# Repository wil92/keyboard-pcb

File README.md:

# keyboard-pcb

A compendium of project about DIY keyboards base on STM32 chips.

> The gerber files are provided and you can use it to replicate the keyboard.

> Also the 3D model for the keyboard is provided in the repository.

## Keyboard Alphanum

This is the first keyboard I made. I decided to get an easy option where I can start my incursion on this work of keyboards.
This keyboard could be used as a USB Hub and is a fun project to be made.

## Keyboard Personal

This is a version of 75% keyboard (with some variations).

## Keyboard Split

tbd

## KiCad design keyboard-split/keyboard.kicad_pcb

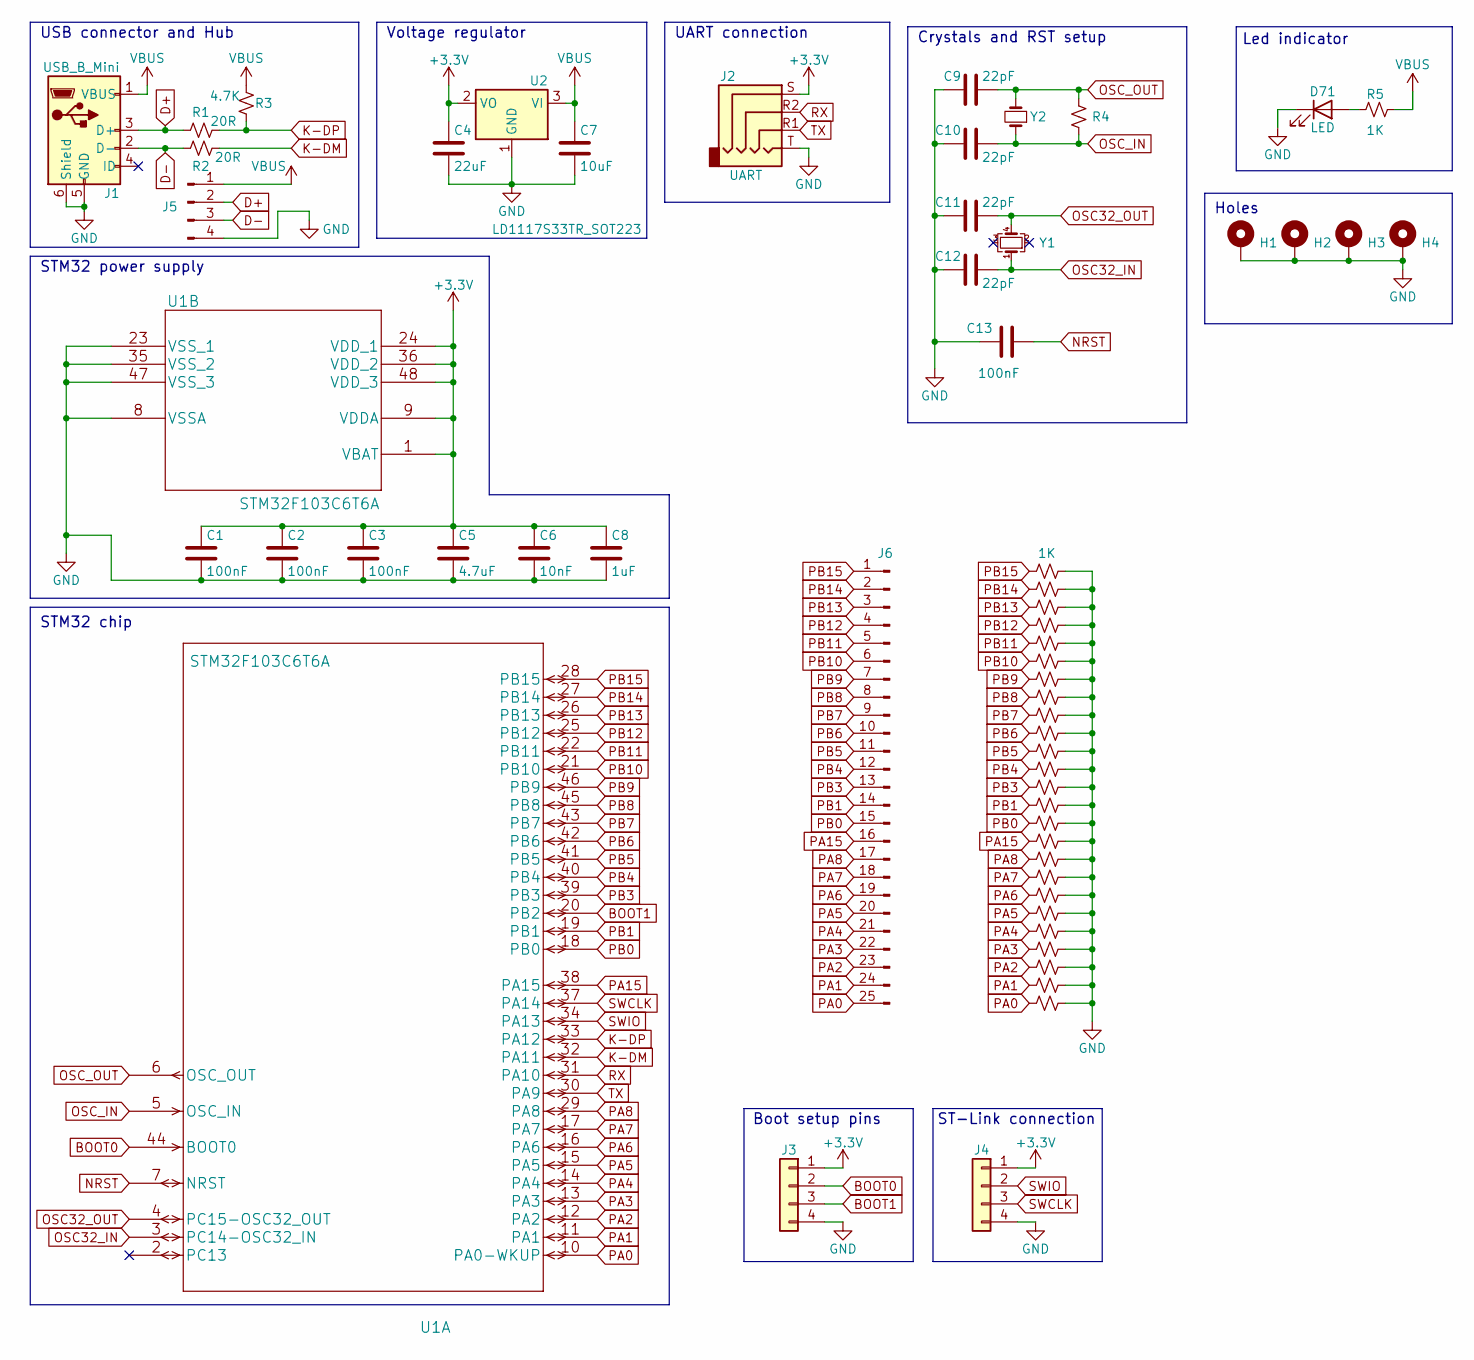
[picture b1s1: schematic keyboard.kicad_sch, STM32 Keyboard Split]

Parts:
C1, C2, C3, C13: 100nF; C_0805_2012Metric
C4: 22uF; C_1206_3216Metric
C5: 4.7uF; C_0805_2012Metric
C6: 10nF; C_0805_2012Metric
C7: 10uF; C_1206_3216Metric
C8: 1uF; C_0805_2012Metric
C9, C10, C11, C12: 22pF; C_0805_2012Metric
D71: LED; LED_0805_2012Metric
H1, H2, H3, H4: MountingHole; MountingHole_3.2mm_M3_DIN965_Pad
J1: USB_B_Mini; USB_Micro-B_A01SB141B1-245
J2: UART; PJ320D
J3, J4: Conn_01x04; PinHeader_1x04_P2.54mm_Vertical
J5: Conn_01x04_Pin; PinSocket_1x04_P1.27mm_Vertical
J6: Conn_01x25_Pin; PinHeader_1x25_P2.54mm_Vertical
R1, R2: 20R; R_0805_2012Metric
R3: 4.7K; R_0805_2012Metric
R4: R_Small_US; R_0805_2012Metric
R5, R6, R7, R8, R9, R10, R11, R12, R13, R14, R15, R16, R17, R18, R19, R20, R21, R22, R23, R24, R25, R26, R27, R28, R29, R30: 1K; R_0805_2012Metric
U1: STM32F103C6T6A; LQFP-48_7x7mm_P0.5mm
U2: LD1117S33TR_SOT223; SOT-223-3_TabPin2
Y1: Crystal_GND23_Small; Crystal_SMD_SeikoEpson_MC306-4Pin_8.0x3.2mm
Y2: Crystal_Small; Crystal_SMD_Abracon_ABM3-2Pin_5.0x3.2mm

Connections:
+3.3V: C1.1, C2.1, C3.1, C4.1, C5.1, C6.1, C8.1, J2.S, J3.1, J4.1, U1.1 (VBAT), U1.9 (VDDA), U1.24 (VDD_1), U1.36 (VDD_2), U1.48 (VDD_3), U2.2 (VO); also elsewhere on the board
BOOT0: J3.2, U1.44 (BOOT0)
BOOT1: J3.3, U1.20 (PB2)
D+: J1.3 (D+), J5.2, R1.1
D-: J1.2 (D-), J5.3, R2.1
GND: C1.2, C2.2, C3.2, C4.2, C5.2, C6.2, C7.2, C8.2, C9.1, C10.1, C11.1, C12.1, C13.1, D71.1 (K), H1.1, H2.1, H3.1, H4.1, J1.5 (GND), J1.6 (Shield), J2.T, J3.4, J4.4, J5.4, R6.2, R7.2, R8.2, R9.2, R10.2, R11.2, R12.2, R13.2, R14.2, R15.2, R16.2, R17.2, R18.2, R19.2, R20.2, R21.2, R22.2, R23.2, R24.2, R25.2, R26.2, R27.2, R28.2, R29.2, R30.2, U1.8 (VSSA), U1.23 (VSS_1), U1.35 (VSS_2), U1.47 (VSS_3), U2.1 (GND); also elsewhere on the board
K-DM: R2.2, U1.32 (PA11)
K-DP: R1.2, R3.1, U1.33 (PA12)
NRST: C13.2, U1.7 (NRST)
unnamed: D71.2 (A), R5.1
OSC32_IN: C12.2, U1.3 (PC14-OSC32_IN), Y1.1
OSC32_OUT: C11.2, U1.4 (PC15-OSC32_OUT), Y1.4
OSC_IN: C10.2, R4.1, U1.5 (OSC_IN), Y2.1
OSC_OUT: C9.2, R4.2, U1.6 (OSC_OUT), Y2.2
PA0: J6.25, R30.1, U1.10 (PA0-WKUP)
PA1: J6.24, R29.1, U1.11 (PA1)
PA2: J6.23, R28.1, U1.12 (PA2)
PA3: J6.22, R27.1, U1.13 (PA3)
PA4: J6.21, R26.1, U1.14 (PA4)
PA5: J6.20, R25.1, U1.15 (PA5)
PA6: J6.19, R24.1, U1.16 (PA6)
PA7: J6.18, R23.1, U1.17 (PA7)
PA8: J6.17, R22.1, U1.29 (PA8)
PA15: J6.16, R21.1, U1.38 (PA15)
PB0: J6.15, R20.1, U1.18 (PB0)
PB1: J6.14, R19.1, U1.19 (PB1)
PB3: J6.13, R18.1, U1.39 (PB3)
PB4: J6.12, R12.1, U1.40 (PB4)
PB5: J6.11, R11.1, U1.41 (PB5)
PB6: J6.10, R10.1, U1.42 (PB6)
PB7: J6.9, R9.1, U1.43 (PB7)
PB8: J6.8, R17.1, U1.45 (PB8)
PB9: J6.7, R16.1, U1.46 (PB9)
PB10: J6.6, R15.1, U1.21 (PB10)
PB11: J6.5, R14.1, U1.22 (PB11)
PB12: J6.4, R13.1, U1.25 (PB12)
PB13: J6.3, R8.1, U1.26 (PB13)
PB14: J6.2, R6.1, U1.27 (PB14)
PB15: J6.1, R7.1, U1.28 (PB15)
RX: J2.R2, U1.31 (PA10); also elsewhere on the board
SWCLK: J4.3, U1.37 (PA14)
SWIO: J4.2, U1.34 (PA13)
TX: J2.R1, U1.30 (PA9); also elsewhere on the board
VBUS: C7.1, J1.1 (VBUS), J5.1, R3.2, R5.2, U2.3 (VI)

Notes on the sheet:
STM32 chip
STM32 power supply
ST-Link connection
Holes
Led indicator
Boot setup pins
Crystals and RST setup
Voltage regulator
UART connection
USB connector and Hub

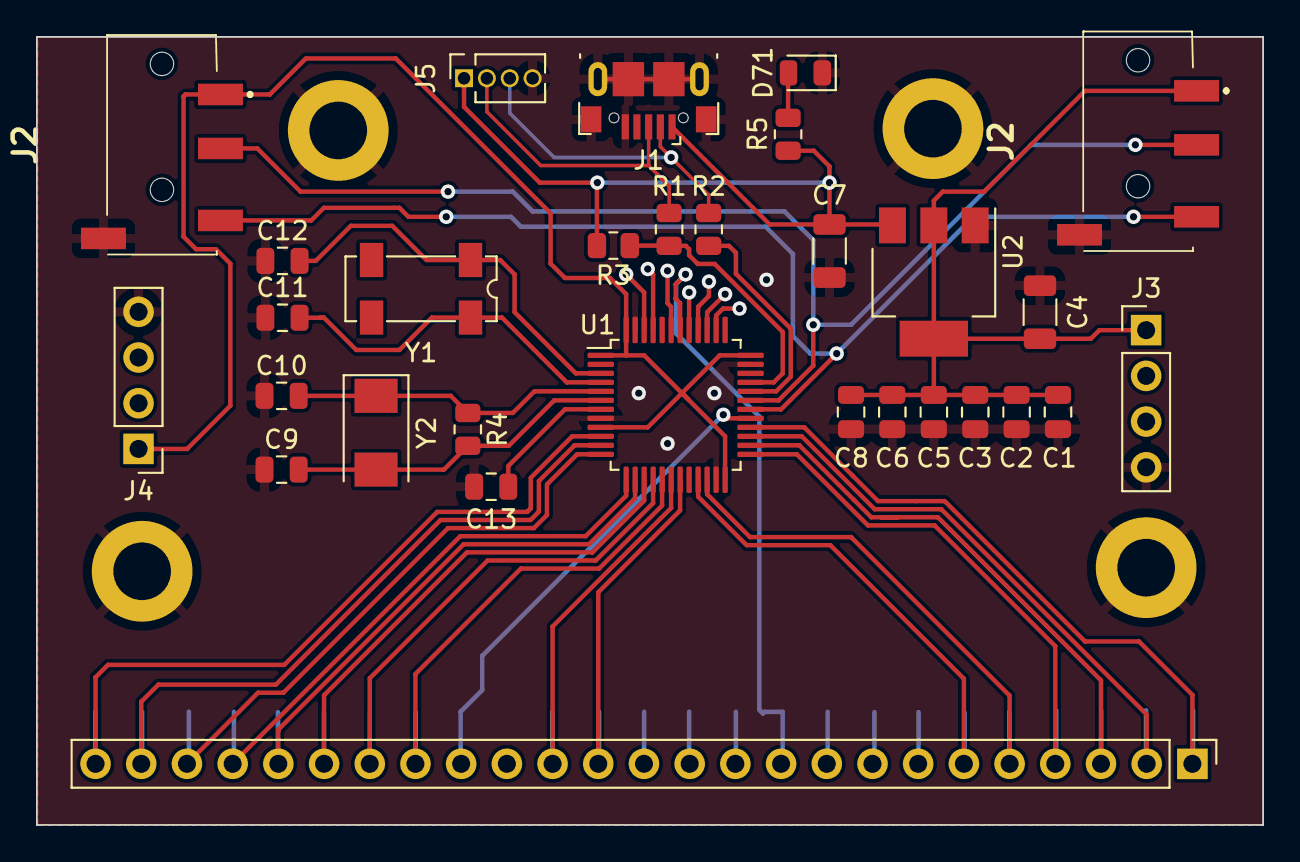
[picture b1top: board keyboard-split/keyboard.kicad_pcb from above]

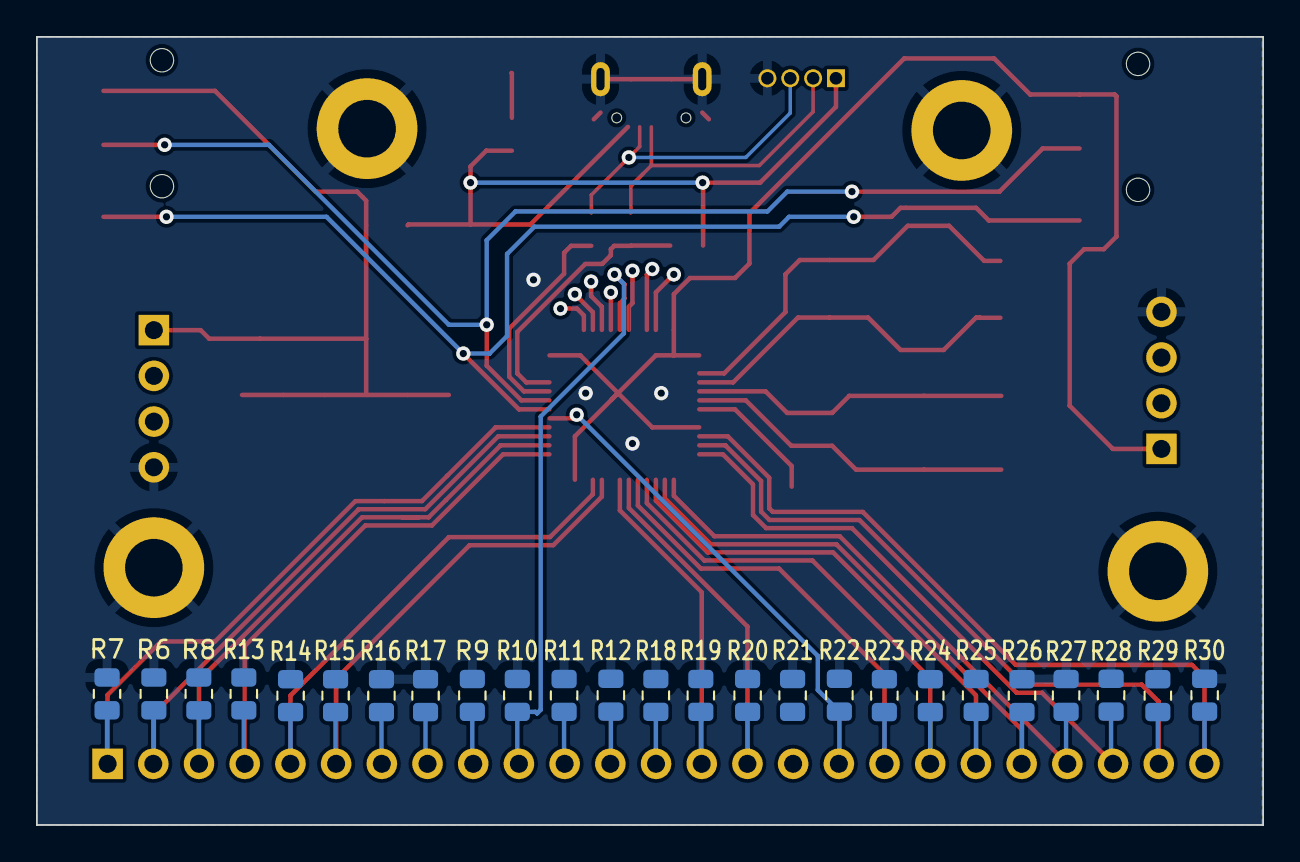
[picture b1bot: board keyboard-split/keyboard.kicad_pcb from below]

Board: 2 copper layers, 68.1 x 43.8 mm, 59 parts (25 on the bottom side), 44 nets.

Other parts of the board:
J2#2: UART; PJ320D

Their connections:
+3.3V: J2#2.S; also elsewhere on the board
GND: J2#2.T; also elsewhere on the board
RX: J2#2.R2; also elsewhere on the board
TX: J2#2.R1; also elsewhere on the board

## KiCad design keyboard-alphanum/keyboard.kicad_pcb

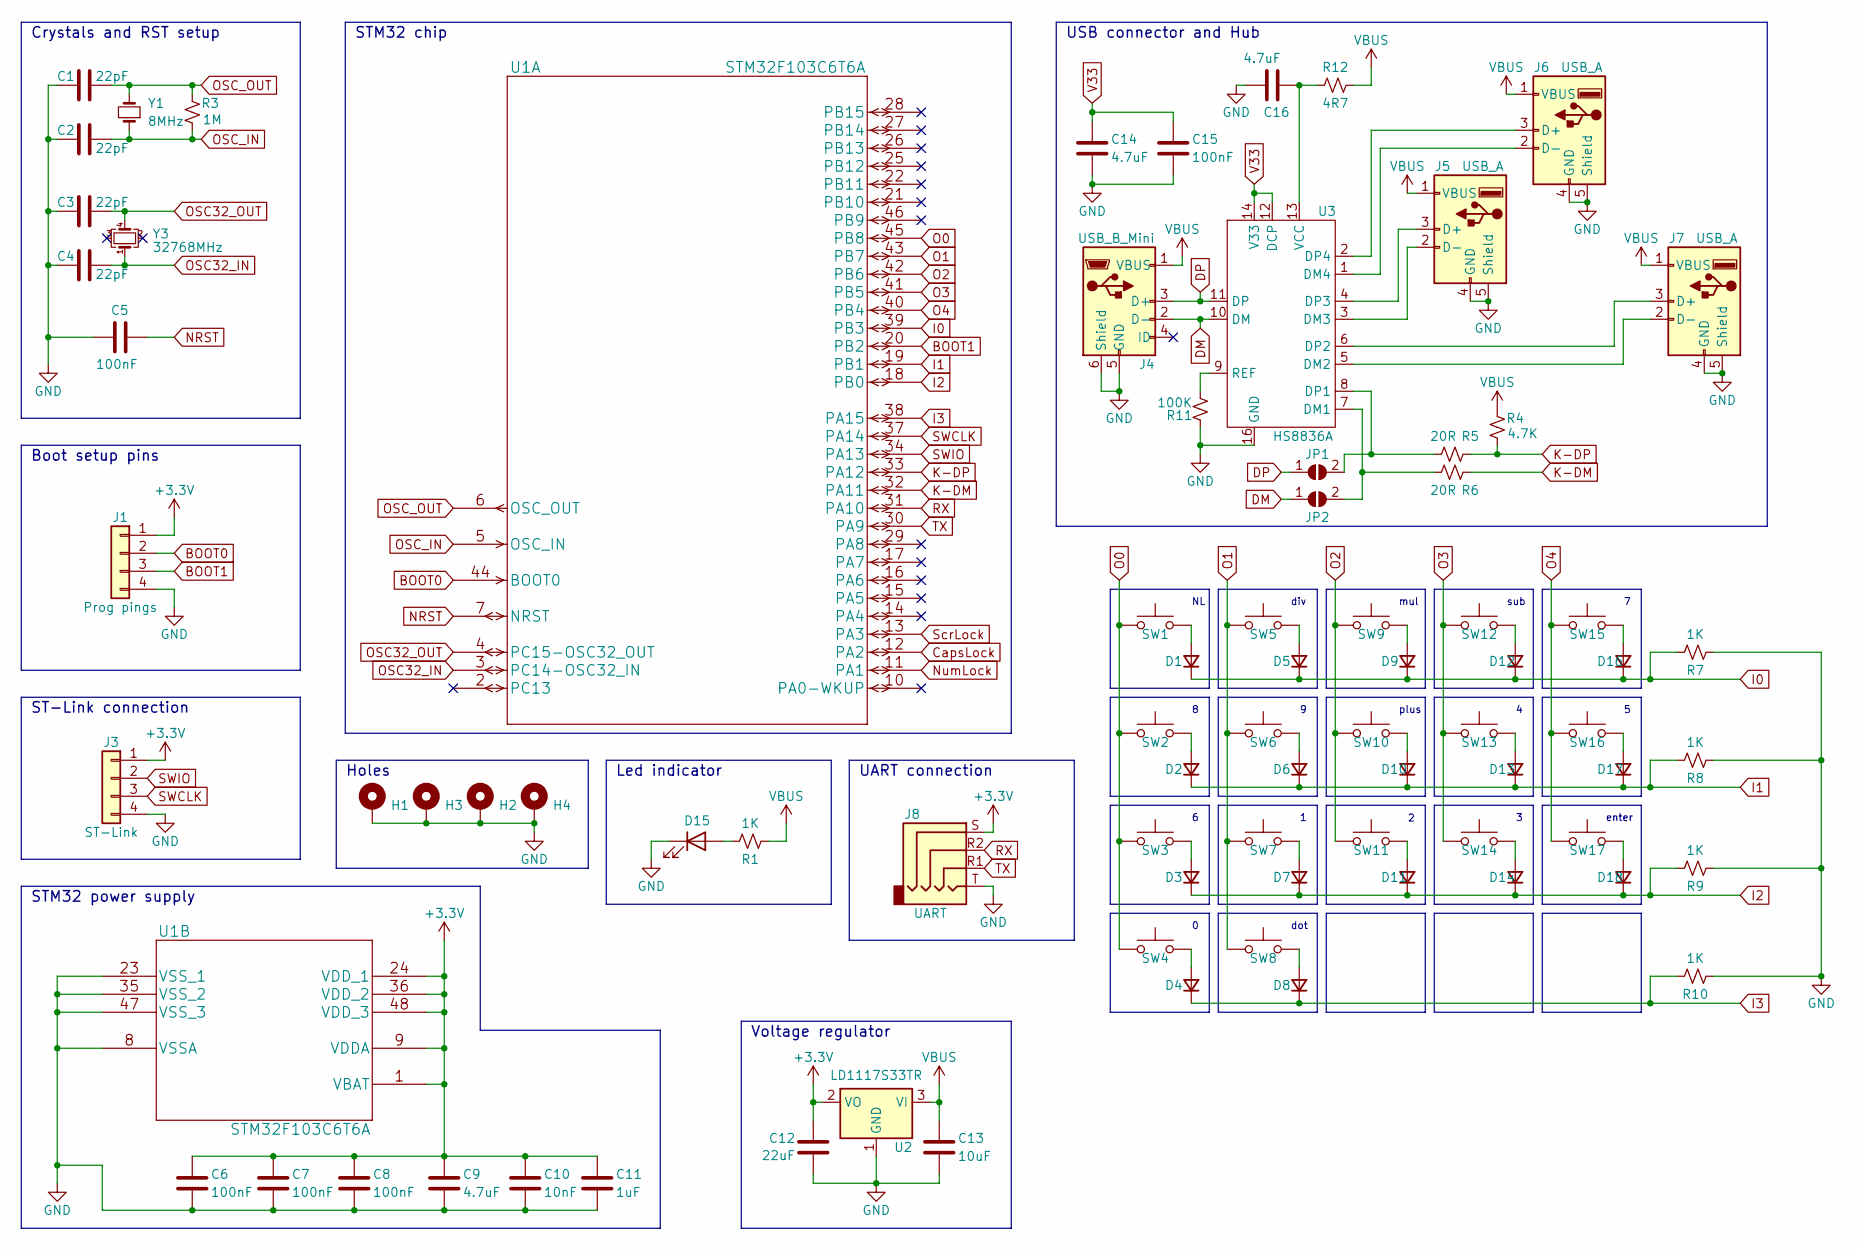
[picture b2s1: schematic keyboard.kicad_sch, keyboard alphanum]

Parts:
C1, C2, C3, C4: 22pF; C_0805_2012Metric
C5, C6, C7, C8, C15: 100nF; C_0805_2012Metric
C9, C14, C16: 4.7uF; C_0805_2012Metric
C10: 10nF; C_0805_2012Metric
C11: 1uF; C_0805_2012Metric
C12: 22uF; C_1206_3216Metric
C13: 10uF; C_1206_3216Metric
D1, D2, D3, D4, D5, D6, D7, D8, D9, D10, D11, D12, D13, D14, D16, D17, D18: D_Small; D_SOD-323
D15: LED; LED_0805_2012Metric
H1, H2, H3, H4: MountingHole; MountingHole_3.2mm_M3_DIN965_Pad
J1: Prog pings; PinHeader_1x04_P2.54mm_Vertical
J3: ST-Link; PinHeader_1x04_P2.54mm_Vertical
J4: USB_B_Mini; USB_Micro-B_A01SB141B1-245
J5, J6, J7: USB_A; USB_A_Molex_105057_Vertical
J8: UART; PJ320D
JP1, JP2: SolderJumper_2_Open; SolderJumper-2_P1.3mm_Open_RoundedPad1.0x1.5mm
R1, R7, R8, R9, R10: 1K; R_0805_2012Metric
R3: 1M; R_0805_2012Metric
R4: 4.7K; R_0805_2012Metric
R5, R6: 20R; R_0805_2012Metric
R11: 100K; R_0805_2012Metric
R12: 4R7; R_0805_2012Metric
SW1: NL; SW_Cherry_MX_PCB_1.00u
SW2: 8; SW_Cherry_MX_PCB_1.00u
SW3: 6; SW_Cherry_MX_PCB_1.00u
SW4: 0; SW_Cherry_MX_PCB_2.00u
SW5: div; SW_Cherry_MX_PCB_1.00u
SW6: 9; SW_Cherry_MX_PCB_1.00u
SW7: 1; SW_Cherry_MX_PCB_1.00u
SW8: dot; SW_Cherry_MX_PCB_1.00u
SW9: mul; SW_Cherry_MX_PCB_1.00u
SW10: plus; SW_Cherry_MX_PCB_2.00u_90deg
SW11: 2; SW_Cherry_MX_PCB_1.00u
SW12: sub; SW_Cherry_MX_PCB_1.00u
SW13: 4; SW_Cherry_MX_PCB_1.00u
SW14: 3; SW_Cherry_MX_PCB_1.00u
SW15: 7; SW_Cherry_MX_PCB_1.00u
SW16: 5; SW_Cherry_MX_PCB_1.00u
SW17: enter; SW_Cherry_MX_PCB_2.00u_90deg
U1: STM32F103C6T6A; LQFP-48_7x7mm_P0.5mm
U2: LD1117S33TR; SOT-223-3_TabPin2
U3: HS8836A; SOP-16_3.9x9.9mm_P1.27mm
Y1: 8MHz; Crystal_SMD_Abracon_ABM3-2Pin_5.0x3.2mm
Y3: 32768MHz; Crystal_SMD_SeikoEpson_MC306-4Pin_8.0x3.2mm

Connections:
+3.3V: C6.1, C7.1, C8.1, C9.1, C10.1, C11.1, C12.1, J1.1, J3.1, J8.S, U1.1 (VBAT), U1.9 (VDDA), U1.24 (VDD_1), U1.36 (VDD_2), U1.48 (VDD_3), U2.2 (VO)
BOOT0: J1.2, U1.44 (BOOT0)
BOOT1: J1.3, U1.20 (PB2)
CapsLock: U1.12 (PA2)
DM: J4.2 (D-), JP2.1 (A), U3.10 (DM)
DP: J4.3 (D+), JP1.1 (A), U3.11 (DP)
GND: C1.1, C2.1, C3.1, C4.1, C5.1, C6.2, C7.2, C8.2, C9.2, C10.2, C11.2, C12.2, C13.2, C14.2, C15.2, C16.1, D15.1 (K), H1.1, H2.1, H3.1, H4.1, J1.4, J3.4, J4.5 (GND), J4.6 (Shield), J5.4 (GND), J5.5 (Shield), J6.4 (GND), J6.5 (Shield), J7.4 (GND), J7.5 (Shield), J8.T, R7.2, R8.2, R9.2, R10.2, R11.2, U1.8 (VSSA), U1.23 (VSS_1), U1.35 (VSS_2), U1.47 (VSS_3), U2.1 (GND), U3.16 (GND)
I0: D1.1 (K), D5.1 (K), D9.1 (K), D12.1 (K), D16.1 (K), R7.1, U1.39 (PB3)
I1: D2.1 (K), D6.1 (K), D10.1 (K), D13.1 (K), D17.1 (K), R8.1, U1.19 (PB1)
I2: D3.1 (K), D7.1 (K), D11.1 (K), D14.1 (K), D18.1 (K), R9.1, U1.18 (PB0)
I3: D4.1 (K), D8.1 (K), R10.1, U1.38 (PA15)
K-DM: R6.2, U1.32 (PA11)
K-DP: R4.1, R5.2, U1.33 (PA12)
NRST: C5.2, U1.7 (NRST)
unnamed: D1.2 (A), SW1.2
unnamed: D2.2 (A), SW2.2
unnamed: D3.2 (A), SW3.2
unnamed: D4.2 (A), SW4.2
unnamed: D5.2 (A), SW5.2
unnamed: D6.2 (A), SW6.2
unnamed: D7.2 (A), SW7.2
unnamed: D8.2 (A), SW8.2
unnamed: D9.2 (A), SW9.2
unnamed: D10.2 (A), SW10.2
unnamed: D11.2 (A), SW11.2
unnamed: D12.2 (A), SW12.2
unnamed: D13.2 (A), SW13.2
unnamed: D14.2 (A), SW14.2
unnamed: D15.2 (A), R1.1
unnamed: D16.2 (A), SW15.2
unnamed: D17.2 (A), SW16.2
unnamed: D18.2 (A), SW17.2
unnamed: J5.3 (D+), U3.4 (DP3)
unnamed: J5.2 (D-), U3.3 (DM3)
unnamed: J6.3 (D+), U3.2 (DP4)
unnamed: J6.2 (D-), U3.1 (DM4)
unnamed: J7.3 (D+), U3.6 (DP2)
unnamed: J7.2 (D-), U3.5 (DM2)
unnamed: JP1.2 (B), R5.1, U3.8 (DP1)
unnamed: JP2.2 (B), R6.1, U3.7 (DM1)
unnamed: R11.1, U3.9 (REF)
unnamed: C16.2, R12.1, U3.13 (VCC)
NumLock: U1.11 (PA1)
O0: SW1.1, SW2.1, SW3.1, SW4.1, U1.45 (PB8)
O1: SW5.1, SW6.1, SW7.1, SW8.1, U1.43 (PB7)
O2: SW9.1, SW10.1, SW11.1, U1.42 (PB6)
O3: SW12.1, SW13.1, SW14.1, U1.41 (PB5)
O4: SW15.1, SW16.1, SW17.1, U1.40 (PB4)
OSC32_IN: C4.2, U1.3 (PC14-OSC32_IN), Y3.1
OSC32_OUT: C3.2, U1.4 (PC15-OSC32_OUT), Y3.4
OSC_IN: C2.2, R3.1, U1.5 (OSC_IN), Y1.1
OSC_OUT: C1.2, R3.2, U1.6 (OSC_OUT), Y1.2
RX: J8.R2, U1.31 (PA10)
SWCLK: J3.3, U1.37 (PA14)
SWIO: J3.2, U1.34 (PA13)
ScrLock: U1.13 (PA3)
TX: J8.R1, U1.30 (PA9)
V33: C14.1, C15.1, U3.12 (DCP), U3.14 (V33)
VBUS: C13.1, J4.1 (VBUS), J5.1 (VBUS), J6.1 (VBUS), J7.1 (VBUS), R1.2, R4.2, R12.2, U2.3 (VI)

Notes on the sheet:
Voltage regulator
STM32 chip
plus
div
Led indicator
USB connector and Hub
sub
Crystals and RST setup
STM32 power supply
Holes
UART connection
enter
Boot setup pins
ST-Link connection
mul
dot

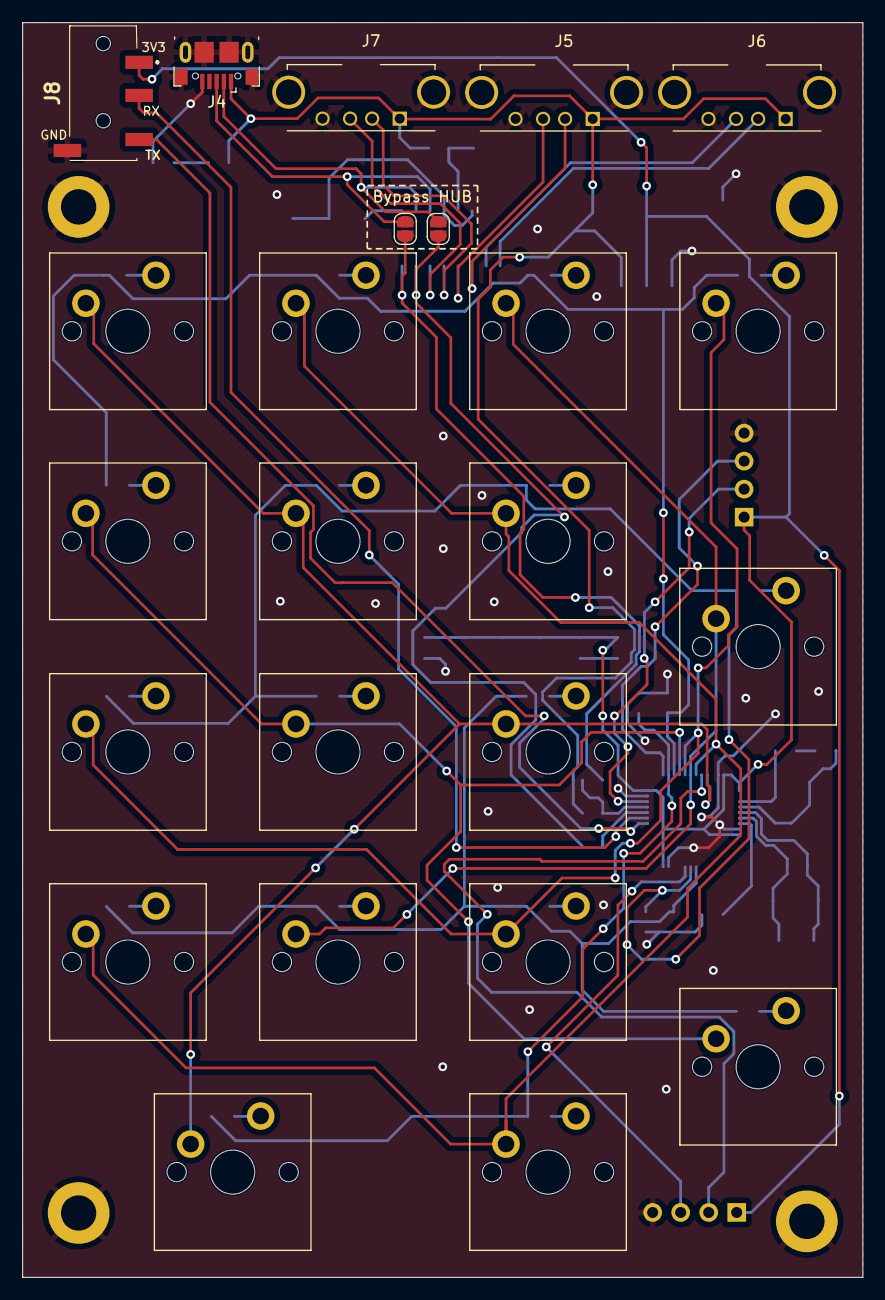
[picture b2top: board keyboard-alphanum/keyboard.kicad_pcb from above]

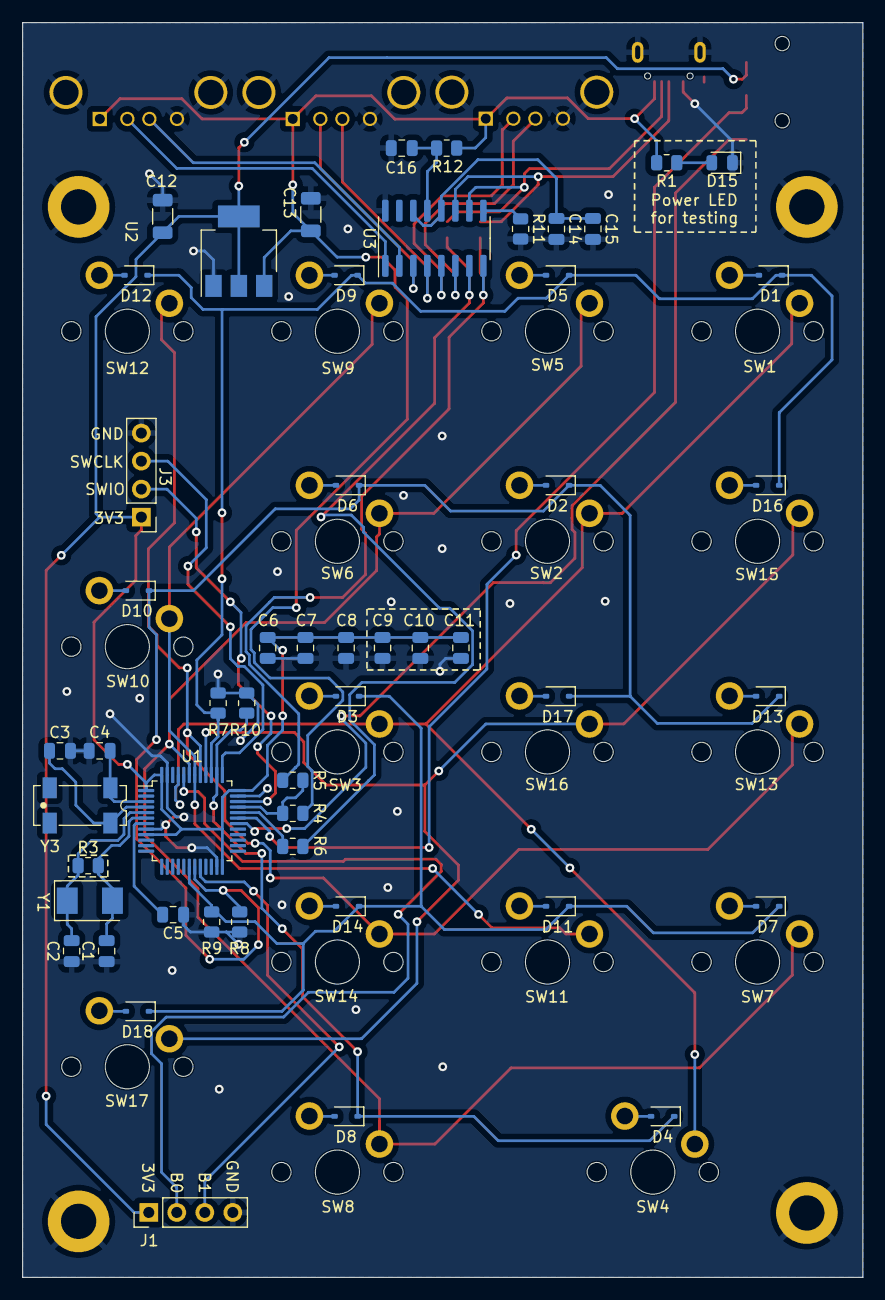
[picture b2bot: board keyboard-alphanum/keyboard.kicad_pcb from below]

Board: 2 copper layers, 76.2 x 113.8 mm, 80 parts (52 on the bottom side), 56 nets.

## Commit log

2022-07-31 Update personal and organize data
2022-07-31 Keyboard alphanum v1.0
2023-01-02 Update keyboar pcb design
2023-07-07 Fix issues and update alphanum keyboard
2024-05-21 Update latest version of keyboard-personal
2024-05-21 Add description to the README.md file
2024-11-20 First version of split keyboard
2024-11-20 Add alphanum description to the readme
